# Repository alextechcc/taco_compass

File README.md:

# Taco Compass
Using a Raspberry Pi, a custom connector Pi hat, a USB GPS and a 9-dof IMU, and scraped google places API data, I have made a plush taco that acts as a compass pointing at the nearest taco restaurant.

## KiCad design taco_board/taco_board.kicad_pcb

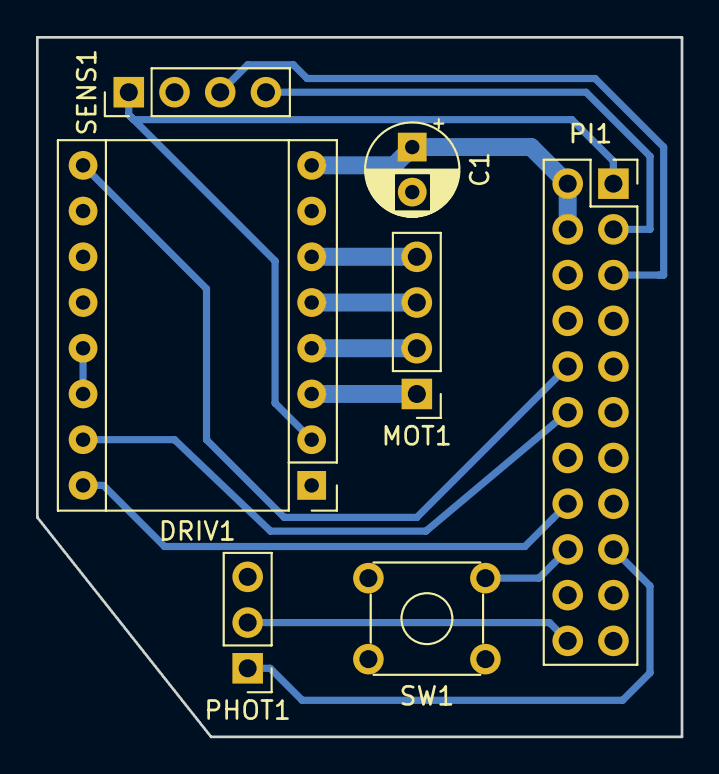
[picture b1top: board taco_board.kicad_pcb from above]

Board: 2 copper layers, 35.8 x 38.9 mm, 7 parts (0 on the bottom side), 16 nets.

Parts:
C1: CP1; CP_Radial_D5.0mm_P2.50mm
DRIV1: Pololu_Breakout_A4988; Pololu_Breakout-16_15.2x20.3mm
MOT1: Stepper_Header; PinHeader_1x04_P2.54mm_Vertical
PHOT1: Photo_Interrupter; PinHeader_1x03_P2.54mm_Vertical
PI1: PI_PartialHeader; PinSocket_2x11_P2.54mm_Vertical
SENS1: MPU_9250_Breakout; PinHeader_1x04_P2.54mm_Vertical
SW1: SW_DPST; SW_TH_Tactile_Omron_B3F-10xx

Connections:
+5V: C1.1, DRIV1.8, PI1.2, PI1.4
/3v3_1: DRIV1.2, PI1.1, SENS1.1
/3v3_2: PHOT1.1, PI1.17
/MOT_DIR: DRIV1.16, PI1.16
/MOT_STEP: DRIV1.15, PI1.12
/SCL: PI1.5, SENS1.3
/SDA: PI1.3, SENS1.4
/~BUT: PI1.18, SW1.3
/~MOT_ENABLE: DRIV1.9, PI1.10
/~PHOTO_SIG: PHOT1.2, PI1.22
GND: C1.2, DRIV1.1, DRIV1.7, DRIV1.10, DRIV1.11, DRIV1.12, PHOT1.3, PI1.6, PI1.9, PI1.20, SENS1.2, SW1.4
unnamed: DRIV1.3, MOT1.1
unnamed: DRIV1.4, MOT1.2
unnamed: DRIV1.5, MOT1.3
unnamed: DRIV1.6, MOT1.4
unnamed: DRIV1.13, DRIV1.14

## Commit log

2018-11-09 Added picture of taco in shell
2019-06-02 Updated ReadMe and touched up files
2019-06-02 Use relative github links and add schematic
